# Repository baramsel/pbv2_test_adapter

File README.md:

# Powerboard v2 test adapter
Carrier PCB to wire bond a Powerboard v2 to.
What looks like a GND plane is actually VIN/VOUT, careful when wiring it up.

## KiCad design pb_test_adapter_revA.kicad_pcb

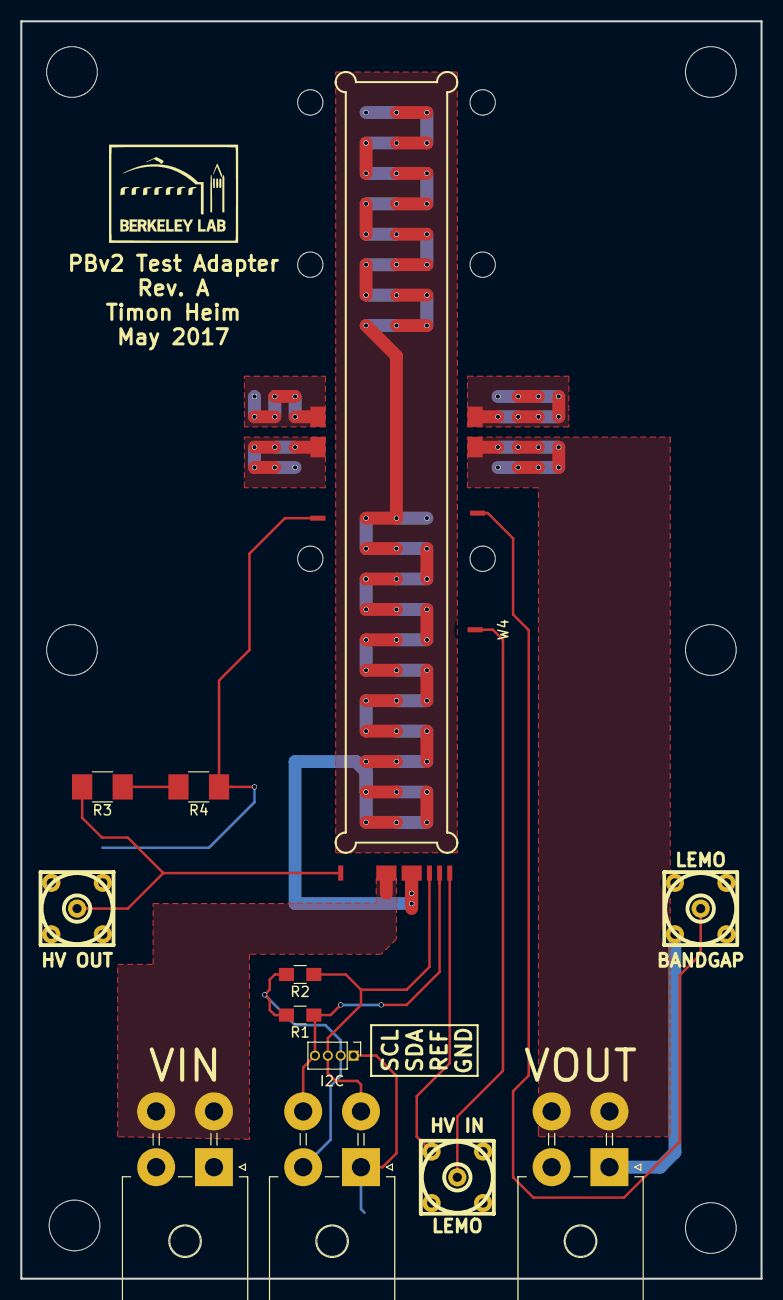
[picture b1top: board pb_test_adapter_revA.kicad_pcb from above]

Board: 2 copper layers, 73.0 x 124.0 mm, 25 parts (1 on the bottom side), 14 nets.

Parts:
BANDGAP: LEMO; lemo_epb00250ntn
HV IN: LEMO; lemo_epb00250ntn
HV OUT: LEMO; lemo_epb00250ntn
I2C: CONN_01X04; Molex_MegaFit_2x02x5.70mm_Angled
JP1: Jumper_NC_Small; GS2
P6: CONN_01X04; Pin_Header_Straight_1x04_Pitch1.27mm
R1, R2: 2k; R_0805_HandSoldering
R3, R4: 5M; R_1210_HandSoldering
VIN: CONN_01X04; Molex_MegaFit_2x02x5.70mm_Angled
VOUT: CONN_01X04; Molex_MegaFit_2x02x5.70mm_Angled
W1, W2, W7, W8, W9, W10: BOND_PAD; Bondpad_Large
W3, W4, W5, W6, W11, W12, W13: BOND_PAD; Bondpad_Small

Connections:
/BANDGAP: BANDGAP.1, W13.1
/HV_IN: HV IN.1, W4.1
/HV_IN_RTN: HV IN.2, W3.1
/HV_OUT: HV OUT.1, R3.2, W11.1
/HV_OUT_RTN: HV OUT.2, R4.1, W12.1
/I2C_GND: I2C.1, JP1.1, P6.1
/I2C_SCL: I2C.4, P6.4, R1.1, W5.1
/I2C_SDA: I2C.3, P6.3, R2.1, W6.1
/I2C_VREF: I2C.2, P6.2, R1.2, R2.2
/VIN: VIN.3, VIN.4, W1.1
/VIN_RTN: VIN.1, VIN.2, W2.1
/VOUT: VOUT.3, VOUT.4, W9.1, W10.1
/VOUT_RTN: BANDGAP.2, VOUT.1, VOUT.2, W7.1, W8.1
unnamed: R3.1, R4.2

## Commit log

2017-06-07 Initial commit, rev.A
